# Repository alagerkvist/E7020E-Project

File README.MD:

# Embbeded Audio Effects

E7020E Embedded System Design is a course giving at Lulea University of Technology. [Link to course syllabus](https://www.ltu.se/edu/course/E70/E7020E/E7020E-Design-av-inbyggda-system-1.67927?kursView=kursplan&l=en)

The purpose of this course is to get a understanding of embedded system and applying that knowledge into designing your own system. Our group did a system that can manipulate audio (adding effects). Where giving an audio input, add some effects and then output it on a speaker.

## Getting Started

* Start by installing Rust for embedded system, follow [this](https://rust-embedded.github.io/book/intro/install.html) guide. 
* Install OpenOCD (version 0.10.0)
* Install arm-none-eabi-gdb (version 8.2.1)
* We are using as of 2019-03-27: rustc 1.34.0-nightly (8a57831a4 2019-02-02)

### Building software
* Clone the repo ``` git clone https://github.com/alagerkvist/E7020E-Project.git ```
* If you would like to use the latest main program run ``` cargo build --release ```
* For examples, run ``` cargo build --example NAME_OF_RS_FILE (codec) ```

## Deployment

* Create FIFO file ``` mkfifo /tmp/itm.log ```
* Start your ITM trace ``` itmdump -f /tmp/itm.log -F ```
* Start OpenOCD ``` openocd -f openocd.cfg ```
* Start gdb ``` arm-none-eabi-gdb target/thumbv7em-none-eabinhf/debug/examples/NAME_OF_RS_FILE -x openocd.gdb ```

## Authors

* **Christoffer Forsberg** - *PCB design*
* **Anders Lagerkvist** - *Programming*
* **Gustav Larsson** - *Programming* 

## Grades
**3**
* Control lamp with PWM signal through UART/potentiometer/button

* **Christoffer Forsberg** - *PWM signal*
* **Anders Lagerkvist** - *ADC for potentiometer*
* **Gustav Larsson** - *Button and UART*

**4**
* Store input siganl in RAM with the help of a button
* Get a sinus wave to output to the codec
* Do an echo with the "signal"
* Show settings on LCD
* Implement I2S/(I2C/SPI) for audio codec

* **Christoffer Forsberg** - *Signal processing, store audio input to RAM with button*
* **Anders Lagerkvist** - *LCD, I2S sine wave output to codec*
* **Gustav Larsson** - *LCD I2C/SPI*

**5**
* Overlay two signals as output
* Integrate different impulse for signal proccessing
* Use an USB as storage

* **Christoffer Forsberg** - *Real time signal processing*
* **Anders Lagerkvist** - *USB implementation*
* **Gustav Larsson** - *Real time signal processing*

## Implemented features

* PWM/LED
* Button
* LCD
* Codec (ish)
* ADC

## Known issues and limitation

* MCUs adc can only read from one potentiometer
* LCD screen has no library yet, so it's a pain in the a** to write to it
* As of now, the codec is inconsistent when writing to it, possible reason to this can be impedance mismatch or wrongfully clock generation 
* PCB layout for 5V to 3.3V regulator is not right implemented
* Footprint for mini-usb type B is placed wrong, should be the other way around (no possibility to mount it on the PCB as of now)
* Codec is in master mode, and should be in slave mode (can be fixed with a pull down resistor instead of a pull up resistor)
* Layout for the potentiometer is too close, needs to seperate more
* Footprint for RCA connector needs to be bigger in their NPTH hole 

## Future work

* Implement ADC so it can be read from three potentiometers
* Library for LCD
* Successfully send data to codec
* Store data from codec into ram
* Sound processing (filter or convolution implementation)
* Store/read data on USB 

## Acknowledgments
PhD Student Cristina Paniagua [Link to profile](https://www.ltu.se/staff/c/cripan-1.167417?l=en)

Professor Per Lindgren [Link to profile](https://www.ltu.se/staff/p/pln-1.11258?l=en)

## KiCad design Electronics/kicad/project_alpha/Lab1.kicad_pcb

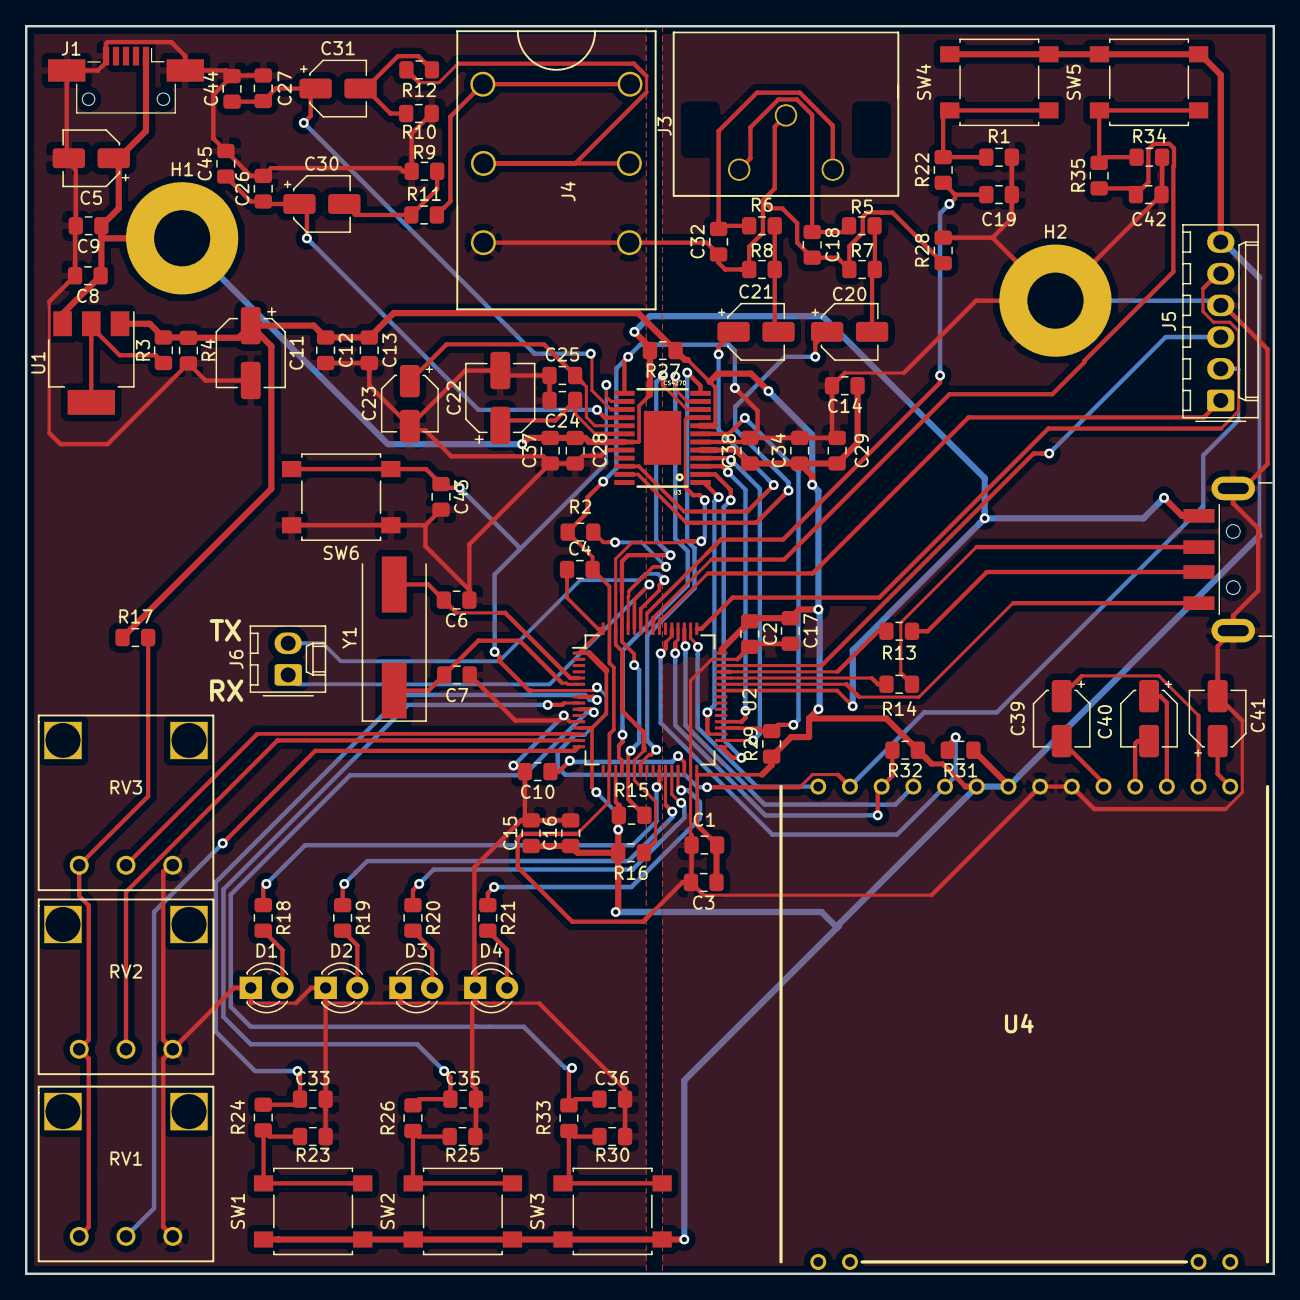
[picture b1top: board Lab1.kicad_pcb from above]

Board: 2 copper layers, 100.0 x 100.0 mm, 106 parts (0 on the bottom side), 74 nets.

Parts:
C1, C2, C3, C4, C8, C9, C10, C12, C13, C14, C16, C19, C24, C25, C28, C29, C33, C34, C35, C36, C42, C43: 100n; C_0805_2012Metric_Pad1.15x1.40mm_HandSolder
C5: 10u; CP_Elec_4x5.4
C6, C7: 18p; C_0805_2012Metric_Pad1.15x1.40mm_HandSolder
C11: 10u; CP_Elec_5x5.9
C15, C37, C38: 1u; C_0805_2012Metric_Pad1.15x1.40mm_HandSolder
C17: 4.7u; C_0805_2012Metric_Pad1.15x1.40mm_HandSolder
C18, C32: 2700p; C_0805_2012Metric_Pad1.15x1.40mm_HandSolder
C20, C21: 3.3u; CP_Elec_4x5.4
C22: 47u; CP_Elec_5x5.4
C23, C30, C31: 10u; CP_Elec_4x5.3
C26, C27, C44, C45: 100p; C_0805_2012Metric_Pad1.15x1.40mm_HandSolder
C39, C40, C41: 1u; CP_Elec_4x5.4
D1, D2, D3, D4: LED; LED_D3.0mm
H1, H2: MountingHole_Pad; MountingHole_4.5mm_Pad
J1: USB_OTG; USB_Mini-B_AdamTech_MUSB-B5-S-VT-TSMT-1_SMD_Vertical
J2: USB_B_Micro; USB_A_remade
J3: Conn_01x03_Female; RCA
J4: Conn_01x06_Female; 6.35_stero_jack_socket
J5: Conn_01x06_Female; Molex_KK-254_AE-6410-06A_1x06_P2.54mm_Vertical
J6: Conn_01x02_Female; Molex_KK-254_AE-6410-02A_1x02_P2.54mm_Vertical
R1, R7, R8, R17, R23, R25, R30, R34: 10k; R_0805_2012Metric_Pad1.15x1.40mm_HandSolder
R2: 10K; R_0805_2012Metric_Pad1.15x1.40mm_HandSolder
R3: 1.8k; R_0805_2012Metric_Pad1.15x1.40mm_HandSolder
R4: 3.3k; R_0805_2012Metric_Pad1.15x1.40mm_HandSolder
R5, R6: 470; R_0805_2012Metric_Pad1.15x1.40mm_HandSolder
R9, R10, R11, R12, R15, R16: 2k2; R_0805_2012Metric_Pad1.15x1.40mm_HandSolder
R13, R14: 22; R_0805_2012Metric_Pad1.15x1.40mm_HandSolder
R18, R19, R20, R21: 330; R_0805_2012Metric_Pad1.15x1.40mm_HandSolder
R22, R24, R26, R33, R35: 1k; R_0805_2012Metric_Pad1.15x1.40mm_HandSolder
R27: 5.1; R_0805_2012Metric_Pad1.15x1.40mm_HandSolder
R28: 0; R_0805_2012Metric_Pad1.15x1.40mm_HandSolder
R29: 47k; R_0805_2012Metric_Pad1.15x1.40mm_HandSolder
R31, R32: 4.7k; R_0805_2012Metric_Pad1.15x1.40mm_HandSolder
RV1, RV2, RV3: 1MEG; rotary_pot
SW1, SW2, SW3, SW4, SW5, SW6: SW_Push; SW_SPST_B3S-1000
U1: LM1117ADJ; SOT-223
U2: STM32F411RETx; LQFP-64_10x10mm_P0.5mm
U3: CS4270
U4: EADOGS102W-6; EA-DOGS102W-6
Y1: 8.0MHz; Crystal_SMD_HC49-SD

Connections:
+3V3: C1.1, C2.1, C3.1, C4.1, C11.1, C12.1, C13.1, C14.1, C15.1, C16.1, C17.1, C29.1, C34.1, C38.1, J5.6, R3.1, R4.1, R15.2, R16.2, R17.1, R27.1, R29.1, R31.1, R32.1, SW1.2, SW2.2, SW3.2, SW4.2, SW5.2, U1.1, U2.1, U2.13, U2.19, U2.32, U2.48, U2.64, U3.5, U3.8, U4.22, U4.23
+5V: C5.1, C8.1, C9.1, C28.2, C37.2, H1.1, J1.1, J2.1, R27.2, U1.3, U2.42, U3.19
/Button1: C33.1, R24.1, U2.8
/Button2: C35.1, R26.1, U2.9
/Button3: C36.1, R33.1, U2.10
/Button4: C19.1, R22.1, U2.57
/Button5: C42.1, R35.1, U2.56
/CODEC_CS: U2.20, U3.11
/CODEC_SPI_MISO: R16.1, U2.22, U2.62, U3.9
/CODEC_SPI_MOSI: U2.23, U3.12
/CODEC_SPI_SCK: R15.1, U2.21, U2.61, U3.10
/I2S_LRCK: U2.33, U3.2
/I2S_MCLK: U2.37, U3.3
/I2S_SCLK: U2.34, U3.4
/I2S_SDIN: U2.35, U3.1
/I2S_SDOUT: R29.2, U2.36, U3.7
/INL: C27.1, C31.1, C44.1, U3.15
/INR: C26.1, C30.1, C45.1, U3.16
/LCD_CS: U2.50, U4.28
/LCD_SPI_MISO: R32.2, U2.52, U4.26
/LCD_SPI_MOSI: R31.2, U2.53, U4.24
/LCD_SPI_SCK: U2.51, U4.25
/LED1: R18.1, U2.26
/LED2: R19.1, U2.27
/LED3: R20.1, U2.28
/LED4: R21.1, U2.29
/NRST: C43.1, J5.2, SW6.2, U2.7, U3.14, U4.27
/OUTL: C21.1, U3.22
/OUTR: C20.1, U3.23
/POT1: RV3.2, U2.14
/POT2: RV2.2, U2.15
/POT3: RV1.2, U2.16
/SWCLK: J5.5, U2.49
/SWDIO: J5.3, U2.46
/SWO: J5.1, U2.55
/USART_RX: J6.1, U2.59
/USART_TX: J6.2, U2.58
/USB_DM: R13.1, U2.45
/USB_DP: R14.1, U2.44
/USB_ID: J2.4, U2.43
GNDA: C5.2, C6.1, C7.1, C8.2, C9.2, C10.2, C11.2, C12.2, C13.2, C15.2, C16.2, C18.2, C22.2, C23.2, C24.2, C25.1, C26.2, C27.2, C28.1, C32.1, C33.2, C35.2, C36.2, C37.1, C43.2, C44.2, C45.2, D1.1, D2.1, D3.1, D4.1, J1.5, J1.6, J3.1, J4.3, J4.6, R4.2, R7.2, R8.2, R9.2, R10.2, R23.2, R25.2, R28.1, R30.2, RV1.3, RV2.3, RV3.3, SW6.1, U2.12, U3.20
GNDD: C1.2, C2.2, C3.2, C4.2, C14.2, C17.2, C19.2, C29.2, C34.2, C38.2, C41.2, C42.2, H2.1, J2.5, J2.6, J5.4, R1.2, R2.2, R28.2, R34.2, U2.18, U2.31, U2.47, U2.63, U3.6, U3.13, U4.20, U4.21
unnamed: C6.2, U2.5, Y1.2
unnamed: C7.2, U2.6, Y1.1
unnamed: C10.1, U2.30
unnamed: C18.1, J3.3, R5.1
unnamed: C20.2, R5.2, R7.1
unnamed: C21.2, R6.2, R8.1
unnamed: C22.1, C24.1, U3.18
unnamed: C23.1, C25.2, U3.17
unnamed: C30.2, R9.1, R11.1
unnamed: C31.2, R10.1, R12.1
unnamed: C32.2, J3.2, R6.1
unnamed: C39.1, U4.16
unnamed: C39.2, U4.19
unnamed: C40.1, U4.17
unnamed: C40.2, U4.18
unnamed: C41.1, U4.15
unnamed: D1.2, R18.2
unnamed: D2.2, R19.2
unnamed: D3.2, R20.2
unnamed: D4.2, R21.2
unnamed: J2.2, R14.2
unnamed: J2.3, R13.2
unnamed: J4.1, J4.4, R11.2
unnamed: J4.2, J4.5, R12.2
unnamed: R1.1, R22.2, SW4.1
unnamed: R2.1, U2.60
unnamed: R3.2, U1.2, U1.4
unnamed: R17.2, RV1.1, RV2.1, RV3.1
unnamed: R23.1, R24.2, SW1.1
unnamed: R25.1, R26.2, SW2.1
unnamed: R30.1, R33.2, SW3.1
unnamed: R34.1, R35.2, SW5.1

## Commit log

2019-02-11 Init commit from me and Anders
2019-02-11 init kicad scheme and footprints for project
2019-02-11 added datasheets for components for the project
2019-02-11 begin designing PCB
2019-02-12 update PCB, not done yet
2019-02-12 update PCB
2019-02-12 started routing PCB
2019-02-12 added a basic delay example in matlab
2019-02-12 Added folder for room impulse responses
2019-02-13 updated readme with some grades and stuff
2019-02-13 finnished PCB routeing, added gerber files
2019-02-15 updated PCB routeing and gerber files
2019-02-18 updated Generic Matlab code to show legends on plots
2019-02-19 toml file is updated and project is setup, can go from here to build the project
2019-02-20 Update README.MD
    updated grades
2019-02-20 Update README.MD
    update readme again
2019-03-12 pot is working with adc
2019-03-12 added exampel for pwm signal using rtfm
2019-03-14 lcd is working now, but still quite messy with the main file, wip
2019-03-14 lcd can print text and pic now
2019-03-18 added lcd to main, not fully working
2019-03-19 some fixes with lcd
2019-03-19 fixed cargo.toml
2019-03-19 hopefully fixed now
2019-03-19 LCD should print duty cycle now (not tested)
2019-03-19 added so it clears before write to screen
2019-03-21 added some exapmle code, looks terrible tho
2019-03-22 clokcs
2019-03-22 loopback works
2019-03-22 iprintln not working now
2019-03-22 got some data...
2019-03-22 debug i2s
2019-03-23 can output sine wave on i2s
2019-03-27 Update README.MD
    some update readme
2019-03-27 added example on how to getstore data from codec. not working at the moment.
2019-03-27 Update README.MD
    some more updates on read me
2019-03-27 Update README.MD
    more updates
2019-03-27 Update README.MD
    update readme
2019-03-27 updated Codec_RAM.rs, sill not working. Slice Error.
2019-03-27 updated Codec_RAM, error is noe fixed. not Tested if functional
2019-03-27 updated Codec_RAM, added send data to codec
2019-03-28 Codec_RAM, can save to RAM but not send to codec, buttons do not work, debugging that. added tmp button file for that
2019-03-28 updated Codec_RAM, buttons works, bug in writing data to codec, debuging that now
2019-03-28 presentation
2019-04-03 worked on i2s2ext, should be enabled now
2019-04-03 change so ext is master tx
2019-04-03 change place of i2sext and i2s
2019-04-04 it works sending data on pb14 and listen on pb15 now
2019-04-04 added i2sext in codec ram
2019-05-22 libm with sample is now compiling. not tested on a MCU yet
2019-05-22 sample.rs is an example using a local sample crate compiled with libm
2019-05-22 small cleanup
2019-05-22 changed it into rtfm
2019-05-22 codec.rs is not working at the moment, working on sample.rs instead (using libm)
2019-05-23 sinus wave kinda work, still some funny things happening
